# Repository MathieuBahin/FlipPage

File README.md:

# FlipPage
Hello everyone,
I would like to share with you today a project that I developed for my needs.

This product let's you turn pages on your tablet with your feets. That's a game changer when you tried one, you no longer have to stop playing to turn a page etc.

I am a guitarist and I have a software (MobileSheets) on my tablet that allows me to display my scores on stage without the famous binder with pages that turn when there is wind.

Similar products exist on the market for a price too high for my taste. I have one but it is no longer compatible with my new tablet.

This page is here to explain how you can build one by yourself.

## Electronics
What do we need ?
- a microcontroler
- 2 buttons
- a bluetooth module

I will be using an Arduino Nano for it's size and ease of programming.
Regarding the bluetooth module we need a module that is "HID" compatible. An HID module is meant to be a keyboard controler, mouse, etc. 

It won't work if your bluetooth module is not "HID" compatible.

After lots of research i found one : the [Adafruit Bluefruit LE UART](https://www.adafruit.com/product/2479)

Based on the nRF51822 bluetooth chip.

I decided to add an extra USB connector as a power input, you can try to use the one from the Arduino Nano if you wish.

### Components used

| Name                  |  Cost |
| --------------------- |:-----:|
| Arduino Nano          |   $2  |
| [Bluefruit SPI BLE](https://www.adafruit.com/product/2479)     | $17.5 |
| USB connector         |  $0.2 |
| [Footswitch](https://www.ebay.fr/itm/262356324402)            |  $4   |
| [Nut](https://www.amazon.fr/gp/product/B00WO7N4PA/)      | $8|
| [Bolt](https://www.amazon.fr/gp/product/B073W7288P/)     | $12|

I used a footswitch like this one :

### KiCad schematic and routing
You will find the files in the folder KiCad.
I printed the PCB at [JLCPCB](https://jlcpcb.com/), reliable and low cost.

## Arduino development
You can use whatever IDE fits you, I used the Arduino IDE.

Add the lib to the libraries folder (generaly in Documents\Arduino\libraries).

Choose the Board : Arduino Nano and the processor that fits your card.

Then connect the Arduino (not the power usb connector) and compile/flash the software. 

You can open the Serial Monitor to see the initialisation.

Now you are done, the only thing left is the casing.

## 3D Printer
My 3D printer is a Creality Ender 3X I'm using black PLA.

You will find the Solidworks files in the folder associated.

You can make the assembly if you wish i didn't upload mine. (Also save the PCB in .step from KiCad to have a full assembly)

The box printing time is around 12h30 at 40%.

The top printing time is around 1h30 at 40%.

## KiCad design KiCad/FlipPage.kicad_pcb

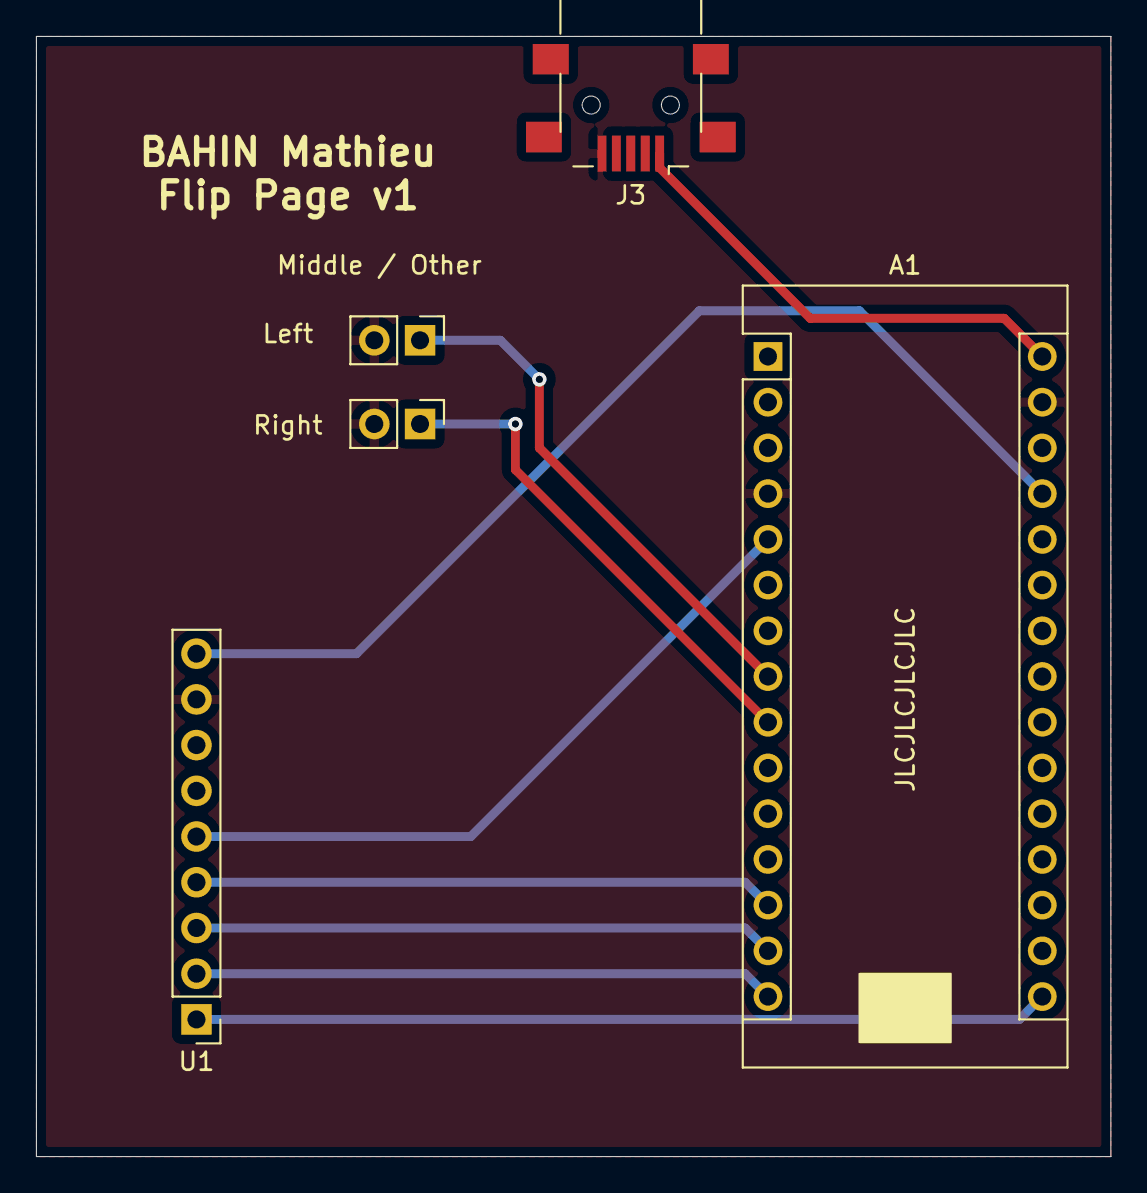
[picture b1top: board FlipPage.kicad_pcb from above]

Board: 2 copper layers, 59.7 x 62.2 mm, 5 parts (0 on the bottom side), 10 nets.

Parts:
A1: Arduino_Nano_v3.x; Arduino_Nano_step
J1, J2: Conn_01x02_Male; PinHeader_1x02_P2.54mm_Vertical
J3: USB_B_Mini; USB_Mini-B_Lumberg_2486_01_Horizontal
U1: Bluefruit_SPI_Bluetooth; PinHeader_1x09_P2.54mm_Vertical

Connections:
unnamed: A1.5, U1.5
unnamed: A1.8, J1.1
unnamed: A1.9, J2.1
unnamed: A1.13, U1.4
unnamed: A1.14, U1.3
unnamed: A1.15, U1.2
unnamed: A1.16, U1.1
unnamed: A1.27, U1.9
unnamed: A1.4, A1.29, J1.2, J2.2, J3.5, U1.8
unnamed: A1.30, J3.1

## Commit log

2021-06-13 Files from the project
2021-06-14 Pictures for readme
2021-06-16 Added Front Silk Info for wiring
2021-06-16 Changes from wiring info addition
2021-06-16 Added KiCad Documentation
2021-06-16 Added libraries files
2021-06-27 [UPDATE] top and box didn't close all the way
    Removed the hole on the top piece and added a hole on the box side
2021-06-27 User should generate his own
2021-06-27 [+] Doc libs
2021-06-27 Modified links of libs
2021-06-27 [+] libs files
2021-06-27 [+] images
2021-09-08 Autoconnect when plugged in no need to forget device on tablet
    Before you had to "forget" the device on the tablet
